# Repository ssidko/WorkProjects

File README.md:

WorkProjects
============

My work projects

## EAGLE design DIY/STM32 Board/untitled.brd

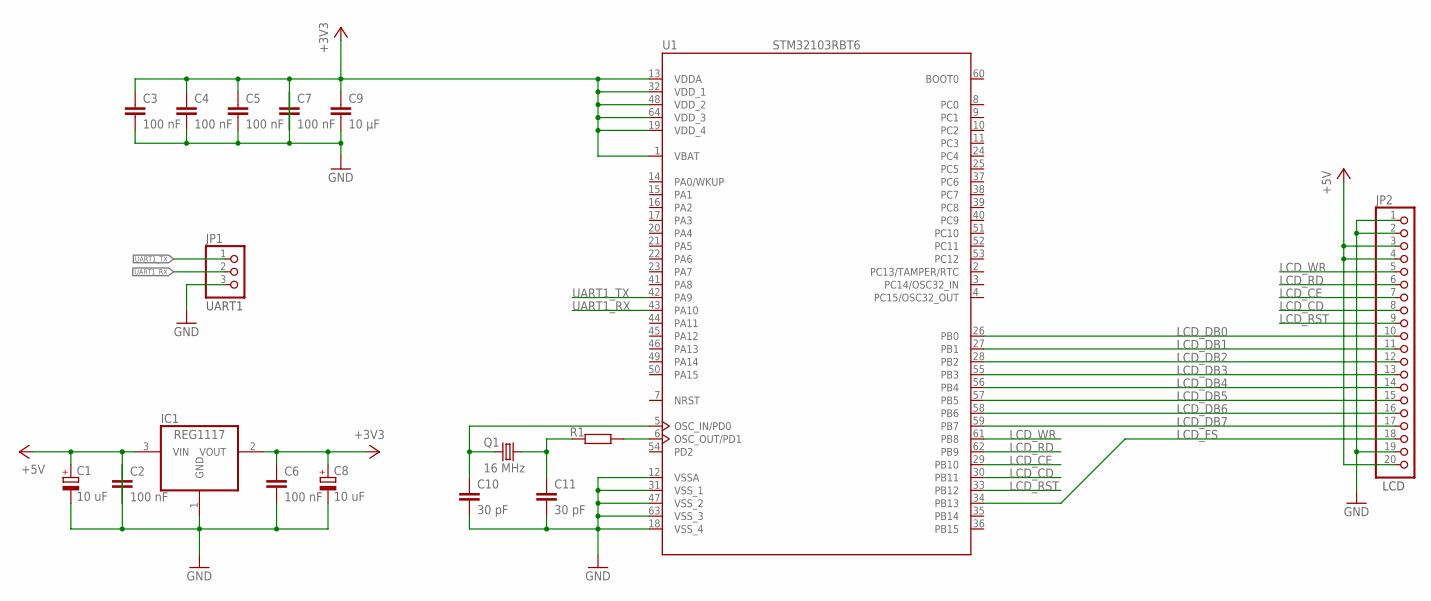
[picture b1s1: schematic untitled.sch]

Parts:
C1, C8: 10 uF; A/3216-18W
C2, C3, C4, C5, C6, C7: 100 nF; C1206
C9: 10 μF; C1206
C10, C11: 30 pF; C1206
IC1: REG1117; SOT223
JP1: PINHD-1X3; 1X03
JP2: PINHD-1X20; 1X20
Q1: 16 MHz; HC49/S
R1: R-EU_R1206; R1206
U1: STM32103RBT6; LQFP64

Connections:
+3V3: C3.1, C4.1, C5.1, C6.1, C7.2, C8.+, C9.1, IC1.2 (VOUT), U1.1 (VBAT), U1.13 (VDDA), U1.19 (VDD_4), U1.32 (VDD_1), U1.48 (VDD_2), U1.64 (VDD_3)
+5V: C1.+, C2.2, IC1.3 (VIN), JP2.3, JP2.4, JP2.20
GND: C1.-, C2.1, C3.2, C4.2, C5.2, C6.2, C7.1, C8.-, C9.2, C10.2, C11.2, IC1.1 (GND), JP1.3, JP2.1, JP2.2, JP2.19, U1.12 (VSSA), U1.18 (VSS_4), U1.31 (VSS_1), U1.47 (VSS_2), U1.63 (VSS_3)
LCD_CD: JP2.8, U1.30 (PB11)
LCD_CE: JP2.7, U1.29 (PB10)
LCD_DB0: JP2.10, U1.26 (PB0)
LCD_DB1: JP2.11, U1.27 (PB1)
LCD_DB2: JP2.12, U1.28 (PB2)
LCD_DB3: JP2.13, U1.55 (PB3)
LCD_DB4: JP2.14, U1.56 (PB4)
LCD_DB5: JP2.15, U1.57 (PB5)
LCD_DB6: JP2.16, U1.58 (PB6)
LCD_DB7: JP2.17, U1.59 (PB7)
LCD_FS: JP2.18, U1.34 (PB13)
LCD_RD: JP2.6, U1.62 (PB9)
LCD_RST: JP2.9, U1.33 (PB12)
LCD_WR: JP2.5, U1.61 (PB8)
unnamed: C10.1, Q1.1, U1.5 (OSC_IN/PD0)
unnamed: C11.1, Q1.2, R1.1
unnamed: R1.2, U1.6 (OSC_OUT/PD1)
UART1_RX: JP1.2, U1.43 (PA10)
UART1_TX: JP1.1, U1.42 (PA9)

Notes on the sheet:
UART1
LCD

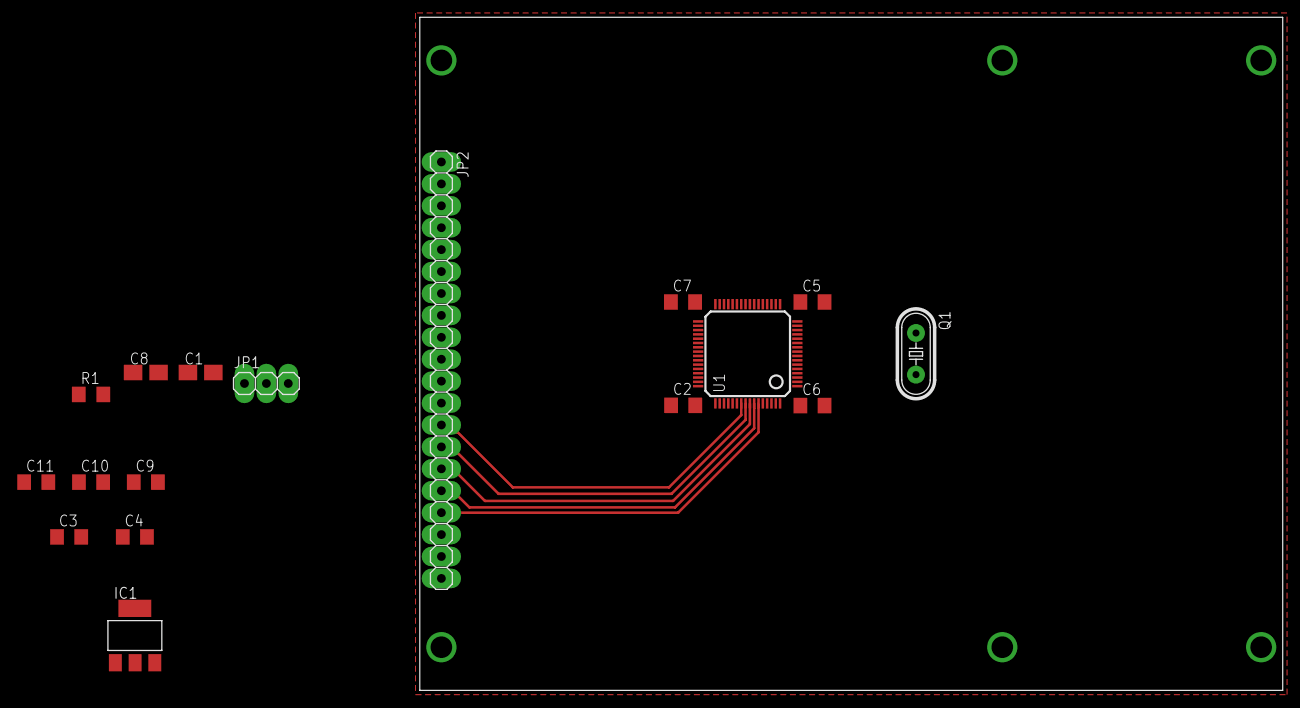
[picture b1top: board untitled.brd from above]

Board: 2 copper layers, 100.0 x 78.0 mm, 17 parts (0 on the bottom side), 22 nets.

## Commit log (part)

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2015-12-01 Terminal v. 0.1
2015-12-01 fix in ComPort::AvailableComPorts() & ComPort::WaitForInputData()
2015-12-01 fix in ServiceInitialize() for detect Leonardo
2015-12-01 add some delays
2015-12-01 GuardSystem v. 0.1.0
2015-12-04 fix IsGuardEnabled()
2015-12-05 add additional flags
    gsm_erase_all_activated;
    guard_sensor_1_activated;
    key_erase_all_activated;
    link_to_slave_losted;
    link_to_master_losted;
2015-12-05 fix slave for Leonardo
2015-12-06 Terminal
2015-12-09 fox for VibroSensor
    active HIGH level
2015-12-10 test
2015-12-10 fix BUGS !!!
    - bug in ComPort::WaitForInputData();
    - memory leaks in ComPort::AvaliableComPorts();
2015-12-25 mover v. 0.0.2
2016-02-18 vs2015 first commit
2016-03-18 add VHDX specification
2016-03-25 Ntfs
2016-04-06 dhfs ++
2016-04-08 dhfs 0.1.0
2016-04-11 hikvision
2016-04-25 HIKV 0.0.1
2016-04-28 DVR ++
2016-05-06 GSys new version
2016-05-18 GuardSys debug trace disable in master module
2016-05-18 GuardSys fix ExecuteScript();
2016-05-18 GuardSys fix ComPort::Open()
2016-05-19 GuardSys critical fixes!!!
    ComPort::WaitForInputData();
2016-05-19 GuardSys Release
2016-06-20 gitignore
2016-11-06 G2FDB recovery v.0.0.0.1
2016-11-15 DVR gui 0.0.1
2016-11-22 detect video size WxH
2016-11-24 BufferedFile reimplemented
2016-11-25 Add Drive size info to comboBox.
2016-11-25 Decrease size precision in drive combobox
2016-11-29 exclude *.bat files from cvs git
2016-11-30 fix bug with max file size
2016-12-02 dvr 0.0.2
2016-12-08 fix bug with wrong Video Resolution
2016-12-13 DHFS: remove old implementation
2017-01-13 Hikvision fix
2017-01-24 add ARM project
2017-01-24 arm ++
2017-02-20 new project
2017-03-02 DVR: add dcH264
2017-03-18 add nuuo
2017-03-20 nuuo
2017-03-21 nuuo++
2017-04-03 dch264
2017-05-05 zfs testing
2017-07-26 RAR recovery v0.0.2
2017-08-30 DVR add offset lineEdit
2017-08-30 add out_of_range check for bitstream_reader
2017-10-18 fix bug in dcH264::FRAME_HEADER::IsValid(void)
2018-01-22 ReadDataBlock2()
2018-01-22 fix in: ReadDataBlock2()
2018-01-23 ZfsObjectDataSaver()
2018-03-15 ziprec
2018-04-02 vs2017
2018-05-30 1cv8
2018-06-13 add stm32-template
2018-06-14 stm32-template
2018-06-16 stm32-template: fix makefile
2018-06-16 fix makefile
2018-08-10 basic functionality
2018-08-10 basic ++
2018-08-10 fix bag: add in_progress variable for correct work wait_for_completed_all_tasks()
2018-08-12 remove tsqueue
2018-08-12 implement test for basic funcionality
2018-08-12 finish
2018-08-12 fixes in worker_thread() and in start_worker_pool()
